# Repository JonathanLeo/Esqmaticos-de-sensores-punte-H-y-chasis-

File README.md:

# Esqmaticos-de-sensores-punte-H-y-chasis-
Esquemas de carro seguidor de linea

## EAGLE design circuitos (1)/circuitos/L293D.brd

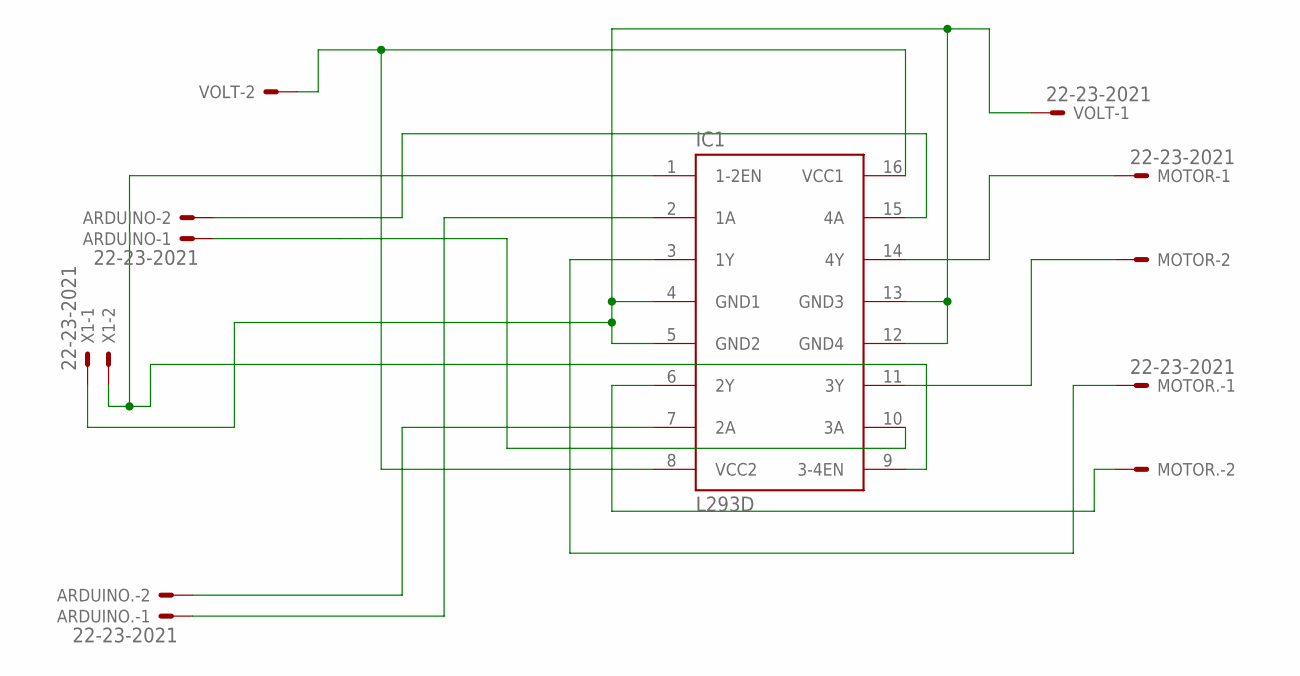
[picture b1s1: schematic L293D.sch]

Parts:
ARDUINO, ARDUINO.: 22-23-2021
IC1: L293D; DIL16
MOTOR, MOTOR.: 22-23-2021
VOLT: 22-23-2021
X1: 22-23-2021

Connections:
GND: IC1.4 (GND1), IC1.5 (GND2), IC1.12 (GND4), IC1.13 (GND3), VOLT.1, X1.1
unnamed: IC1.14 (4Y), MOTOR.1
unnamed: IC1.11 (3Y), MOTOR.2
unnamed: IC1.3 (1Y), MOTOR..1
unnamed: IC1.6 (2Y), MOTOR..2
unnamed: ARDUINO.2, IC1.15 (4A)
unnamed: ARDUINO.1, IC1.10 (3A)
unnamed: IC1.8 (VCC2), IC1.16 (VCC1), VOLT.2
unnamed: ARDUINO..1, IC1.2 (1A)
unnamed: ARDUINO..2, IC1.7 (2A)
unnamed: IC1.1 (1-2EN), IC1.9 (3-4EN), X1.2

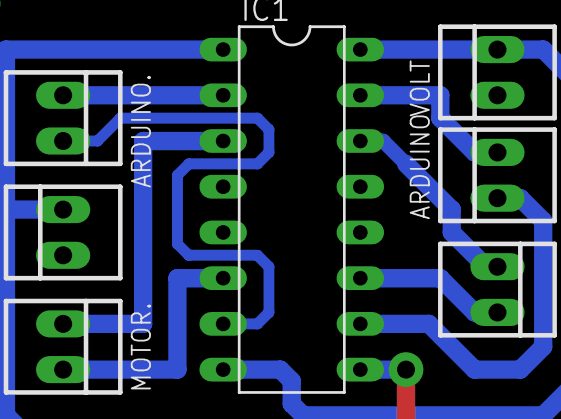
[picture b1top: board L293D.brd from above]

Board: 2 copper layers, 7 parts (0 on the bottom side), 11 nets.

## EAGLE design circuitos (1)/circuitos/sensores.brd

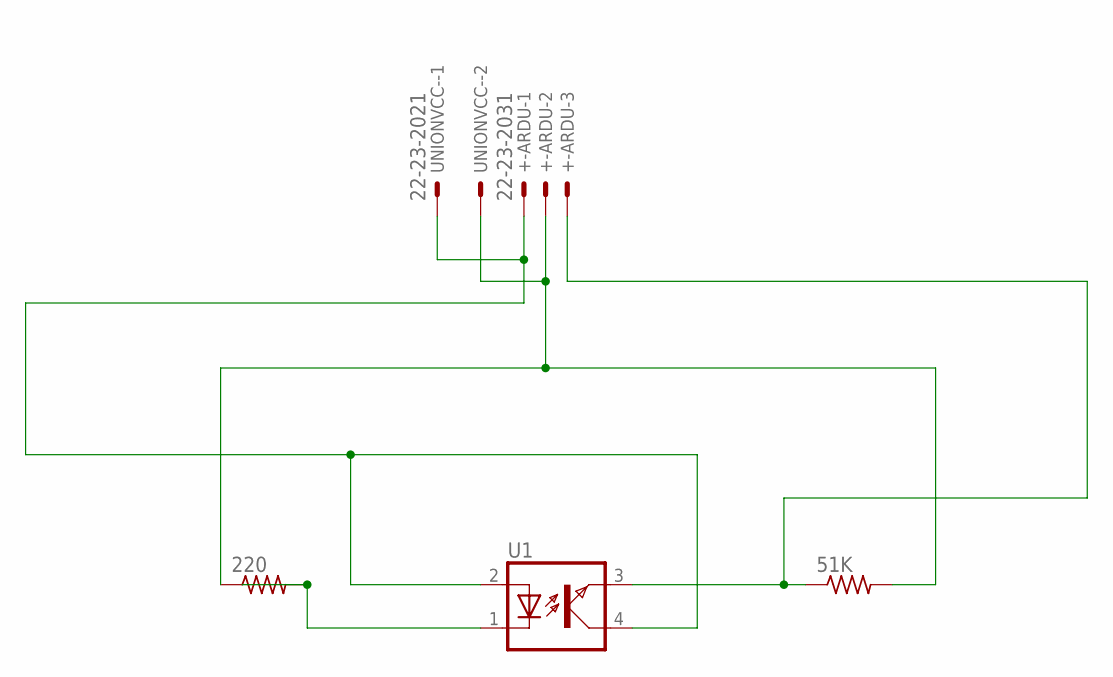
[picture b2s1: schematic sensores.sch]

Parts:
51K, 220: R-US_0207/10; 0207/10
+-ARDU: 22-23-2031
U1: CNY70
UNIONVCC-: 22-23-2021

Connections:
unnamed: 220.2, U1.1
unnamed: 51K.1, +-ARDU.3, U1.3
unnamed: 51K.2, 220.1, +-ARDU.2, UNIONVCC-.2
unnamed: +-ARDU.1, U1.2, U1.4, UNIONVCC-.1

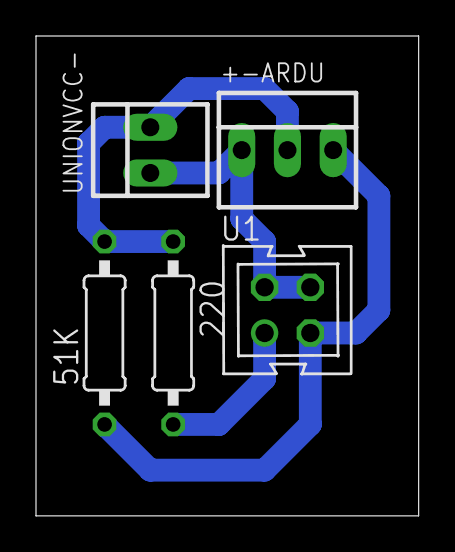
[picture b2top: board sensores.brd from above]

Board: 2 copper layers, 21.3 x 26.7 mm, 5 parts (0 on the bottom side), 4 nets.

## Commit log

2018-06-08 Esquematicos
